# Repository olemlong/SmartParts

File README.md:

# SmartParts
A smart and glowing storage system for electronic components.  

https://www.youtube.com/watch?v=v1Y57d32keY

Ever since I started working with electronics, the pile of parts has been growing to the point where it took forever to find the correct part. The first step in solving this madnes was to get a cabinet and labelmaker. 
With the cabinet stacked with components, and each drawer labeled, I saw the problem as history.

As a few months passed by, the cabinet was full and i needed another cabinet to store more parts. Bought another cabinet, labeled each drawer with the components that was inside. This repeated itself until i had six cabinets all labeled. 

Now instead of searching in a desk drawer filled with all kinds of parst, i searched 6 cabinets for the correct labeled drawer. This became a pain. So i started thinking of a system that could indicate the correct drawer based on a search. This is when the SmartParts system was born.

The hardware requirements:  
-Raspberry Pi (for running the MySql and MQTT server)  
-Esp8266 controller (one controller for each cabinet)  
-WS2812b LED (one for each drawer)  
-LED PCB (one for each row in the cabinet)  
-WiFi

PCB

The LED PCB is optional. You could always buy a roll of the WS2812b leds on ebay and cut it to length. Just a warning, this is what i did in the first cabinet and why i designed the PCB, it is alot of work, the double sided tape falls off and it is a bitch to cut and solder each led.

Cabinet controller (ESP8266)  

This controls the cabinet. When the controller connects to the wifi network, the controller is ready for data input.  
It subscribes to a topic that coresponds to the cabinet number. When the client software publishes data on this topic, the controller will light up leds according to this data. I use one 230v -> 5v 1A power supply for each cabinet (2 pin plug). The 3 pin plug is 5v, GND and data for the leds.  

Server 

I built a little casing for my Raspberry with a screen showing load and IP address.  
You can use whatever casing you want.  You can run what image you want, as long as it runs an MySql server and an MQTT server.

Cabinet layout

PCB mounting in cabinet

Software requirements:
Arduino IDE with support for ESP8266 + some libs (se source)
Python 3 with paho mqtt, mysql connector and PyQy5.  
   
How it all works  
  
  All the parts are stored in a MySql database. Each part has coordinates coresponding to the placement in the cabinets, like an address. This address is composed of four values (W,X,Y,Z).  
W -The cabinet coordinate. 1 = cabinet 1, 2 = cabinet 2, and so on.  
X -The column coordinate. 1 = column 1, 2 = column 2, and so on. I only have 5 columns in my cabinets.  
Y -The row coordinate. 1 = row 1, 2 = row 2, and so on.   
Z -The compartment coordinate. Each drawer can be devided into 4 compartments.   

The Flow of data.  

Whats with the colors?  
When a search is done, the drawers light up with a color. The color indicates the compartment in the drawer the component is in.  
Red empty drawer.  
Yellow first compartment.  
Green second compartment.  
Blue third compartment.  
Purple forth compartment.

https://www.youtube.com/watch?v=v1Y57d32keY

https://www.youtube.com/watch?v=QyOVx2Oqz8I

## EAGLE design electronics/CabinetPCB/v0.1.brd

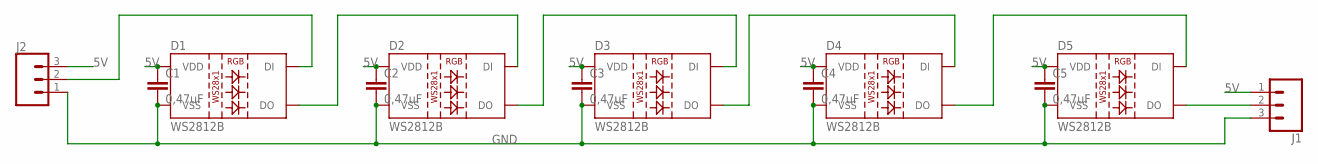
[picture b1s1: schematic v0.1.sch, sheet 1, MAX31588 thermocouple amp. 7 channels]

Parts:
C1, C2, C3, C4, C5: 0,47uF; 1206
D1, D2, D3, D4, D5: WS2812B
J1, J2: CONN_03JST-PTH; JST-3-PTH

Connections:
5V: C1.1, C2.1, C3.1, C4.1, C5.1, D1.1 (VDD), D2.1 (VDD), D3.1 (VDD), D4.1 (VDD), D5.1 (VDD), J1.1, J2.3
GND: C1.2, C2.2, C3.2, C4.2, C5.2, D1.3 (VSS), D2.3 (VSS), D3.3 (VSS), D4.3 (VSS), D5.3 (VSS), J1.3, J2.1
unnamed: D1.2 (DO), D2.4 (DI)
unnamed: D2.2 (DO), D3.4 (DI)
unnamed: D3.2 (DO), D4.4 (DI)
unnamed: D4.2 (DO), D5.4 (DI)
unnamed: D5.2 (DO), J1.2
unnamed: D1.4 (DI), J2.2

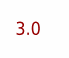
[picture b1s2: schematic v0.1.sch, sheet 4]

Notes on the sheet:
3.0

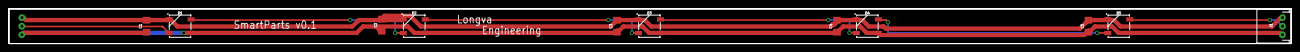
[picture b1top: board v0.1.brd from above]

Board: 2 copper layers, 300.5 x 8.1 mm, 12 parts (1 on the bottom side), 8 nets.

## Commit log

2020-02-01 Add files via upload
    First upload.
2020-02-01 Create readme.md
    first upload
2020-02-01 Add files via upload
    first upload

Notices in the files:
parts and their libraries:
SparkFun-Connectors: Licensing: Creative Commons ShareAlike 4.0 International - https://creativecommons.org/licenses/by-sa/4.0
